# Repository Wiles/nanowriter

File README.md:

# nanowriter
6 key chorded keyboard based on the Microwriter

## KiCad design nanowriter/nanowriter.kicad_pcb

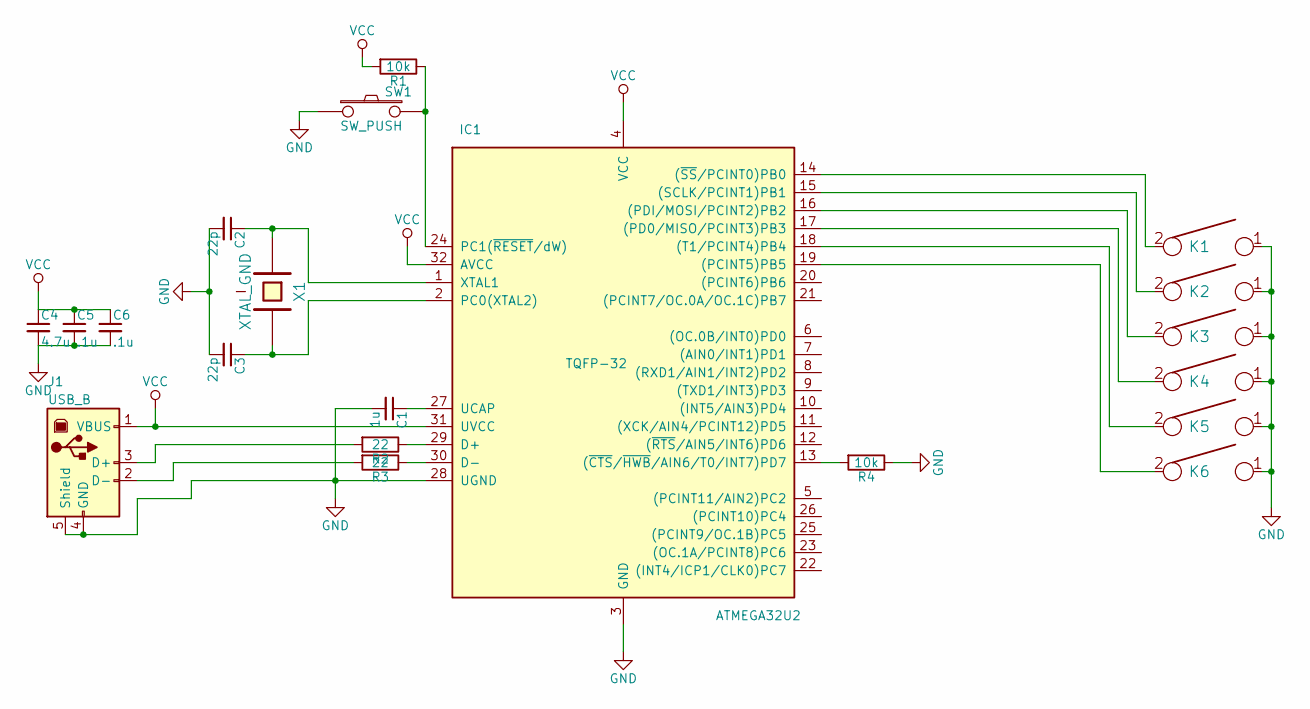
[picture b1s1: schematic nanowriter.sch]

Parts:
C1: 1u; C_0805_HandSoldering
C2, C3: 22p; C_0805_HandSoldering
C4: 4.7u; C_0805_HandSoldering
C5, C6: .1u; C_0805_HandSoldering
IC1: ATMEGA32U2; TQFP-32
J1: USB_B; USB_Micro-B_Molex_47346-0001
K1, K2, K3, K4, K5, K6: KEYSW; MX_PCB_100H
R1, R4: 10k; R_0805_HandSoldering
R2, R3: 22; R_0805_HandSoldering
SW1: SW_PUSH; SW_SPST_TL3342
X1: XTAL_GND; Crystal_SMD_Abracon_ABM8G-4pin_3.2x2.5mm

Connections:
GND: C1.2, C2.2, C3.2, C4.2, C5.2, C6.2, IC1.3 (GND), IC1.28 (UGND), J1.4 (GND), J1.5 (Shield), K1.1, K2.1, K3.1, K4.1, K5.1, K6.1, R4.1, SW1.1
unnamed: C1.1, IC1.27 (UCAP)
unnamed: C2.1, IC1.1 (XTAL1), X1.1
unnamed: C3.1, IC1.2 (PC0(XTAL2)), X1.2
unnamed: IC1.13 ((~CTS~/~HWB~/AIN6/T0/INT7)PD7), R4.2
unnamed: IC1.14 ((~SS~/PCINT0)PB0), K1.2
unnamed: IC1.15 ((SCLK/PCINT1)PB1), K2.2
unnamed: IC1.16 ((PDI/MOSI/PCINT2)PB2), K3.2
unnamed: IC1.17 ((PD0/MISO/PCINT3)PB3), K4.2
unnamed: IC1.18 ((T1/PCINT4)PB4), K5.2
unnamed: IC1.19 ((PCINT5)PB5), K6.2
unnamed: IC1.24 (PC1(~RESET~/dW)), R1.1, SW1.2
unnamed: IC1.29 (D+), R2.1
unnamed: IC1.30 (D-), R3.1
unnamed: J1.2 (D-), R3.2
unnamed: J1.3 (D+), R2.2
VCC: C4.1, C5.1, C6.1, IC1.4 (VCC), IC1.31 (UVCC), IC1.32 (AVCC), J1.1 (VBUS), R1.2

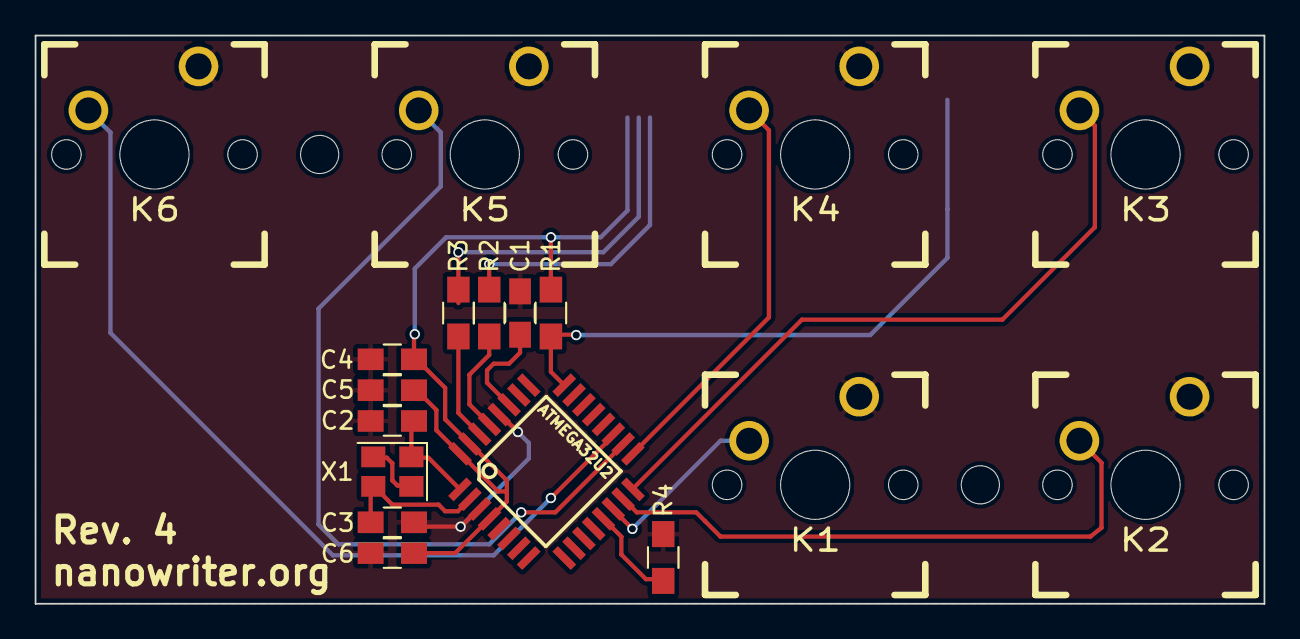
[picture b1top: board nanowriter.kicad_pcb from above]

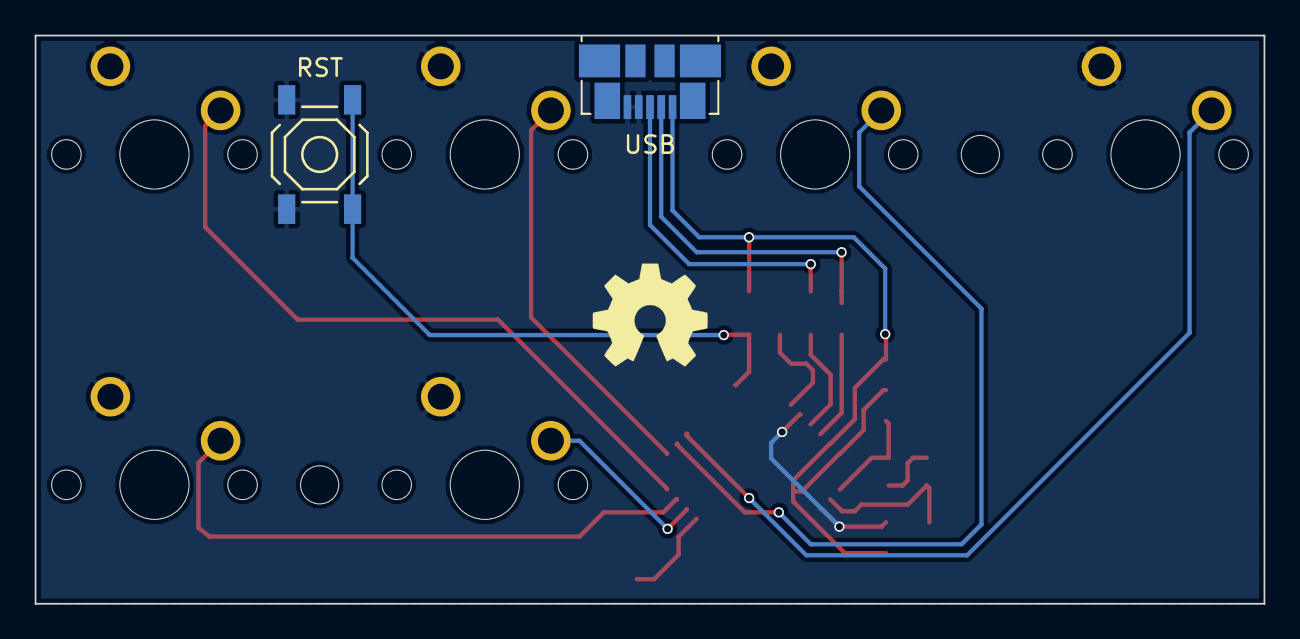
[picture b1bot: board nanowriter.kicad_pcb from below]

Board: 2 copper layers, 70.9 x 32.8 mm, 20 parts (2 on the bottom side), 17 nets.

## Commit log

2017-01-25 Rev 1 pcb
2017-01-26 Changed to port b from port d to match the Pro Micro setup
2017-01-27 First take on logo
2017-01-27 Writing characters to USB as HID device. Removed display output.
2017-01-28 Change use of Keyboard.write to Keyboard.press and Keyboard.release
2017-01-28 Added numeric layer
2017-01-28 Added punctuation
2017-01-28 Added capital layer
2017-01-28 Backspace
2017-01-28 Replaced capital layer with shift toggling
2017-01-29 Added support for meta characters and more whitespace characters
2017-01-29 Added esc key
2017-02-12 Rev. 2 board
    - Minimized dimension
    - Added mounting holes
    - Added reset switch with pullup
    - Fixed pins 13-24 on pro-micro being backwards
2017-02-12 Added text to logo
2017-03-13 Rev 2 switch plate
2017-03-13 PCB rev 3. Changed from Pro Micro based design to directly using an Atmega32u2
2017-05-06 Updated code for atmega32u2
2017-05-06 Removed unused serial begin
2017-06-18 PCB rev 4. Changed to all smd usb port.
2017-07-30 Ignore build artifacts
2017-07-30 erase and flash makefile targets
2017-07-30 Relicensed to Apache 2.0
2019-11-25 Create CNAME
2019-11-25 Created placeholder index.html
2019-11-25 Added logo to website
2020-01-08 Added image to repo
2020-01-08 Added image to readme
